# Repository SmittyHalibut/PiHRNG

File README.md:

# PiHRNG
#### It's pronounced "Pi Ring," or perhaps "Pie Ring" if you'd prefer.

A hardware random number generator on a Raspberry Pi hat.

More here later. (Famous last words, by @SmittyHalibut)

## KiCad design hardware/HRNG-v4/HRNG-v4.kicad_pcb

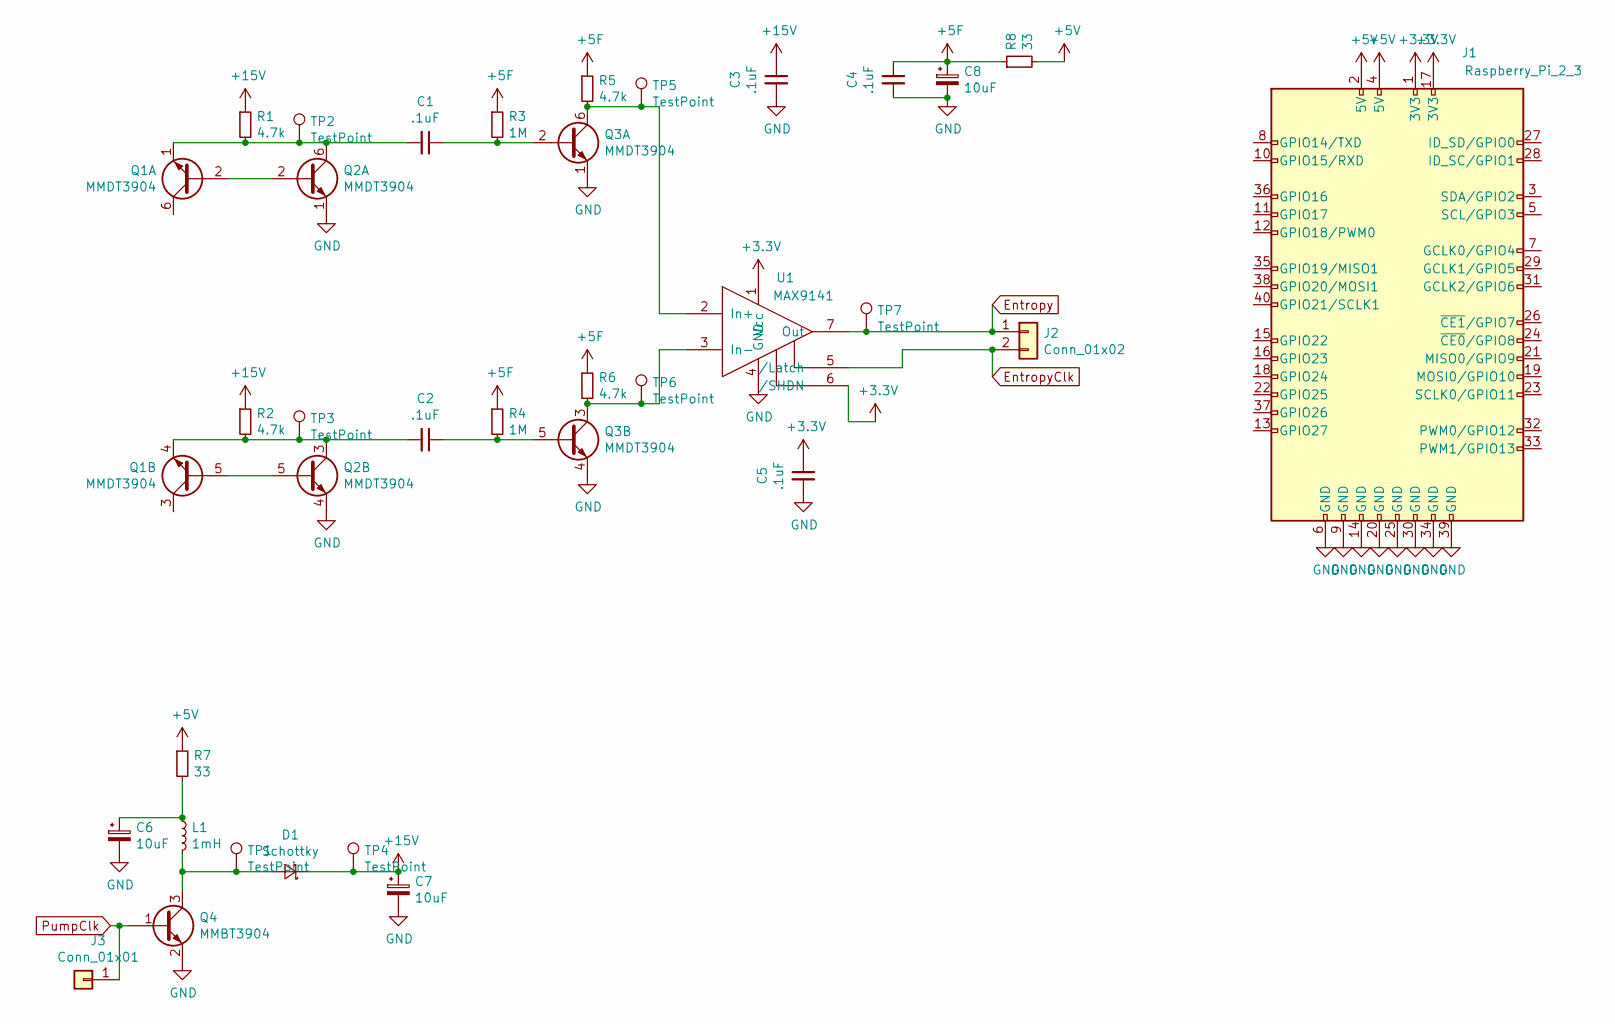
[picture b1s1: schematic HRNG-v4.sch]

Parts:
C1, C2, C3, C4, C5: .1uF; C_1206_3216Metric_Pad1.42x1.75mm_HandSolder
C6, C7, C8: 10uF; CP_Radial_D6.3mm_P2.50mm
D1: Schottky; D_1206_3216Metric_Pad1.42x1.75mm_HandSolder
J1: Raspberry_Pi_2_3; Raspberry_Pi_Zero_Socketed_THT_FaceDown_MountingHoles
J2: Conn_01x02; PinHeader_1x02_P2.54mm_Vertical
J3: Conn_01x01; PinHeader_1x01_P2.54mm_Vertical
L1: 1mH; L_1206_3216Metric_Pad1.42x1.75mm_HandSolder
Q1, Q2, Q3: MMDT3904; SOT-363_SC-70-6_Handsoldering
Q4: MMBT3904; SOT-23
R1, R2, R5, R6: 4.7k; R_1206_3216Metric_Pad1.42x1.75mm_HandSolder
R3, R4: 1M; R_1206_3216Metric_Pad1.42x1.75mm_HandSolder
R7, R8: 33; R_1206_3216Metric_Pad1.42x1.75mm_HandSolder
TP1, TP2, TP3, TP4, TP5, TP6, TP7: TestPoint; TestPoint_Pad_D1.5mm
U1: MAX9141; SOIC-8_3.9x4.9mm_P1.27mm

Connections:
+3V3: C5.1, J1.1 (3V3), J1.17 (3V3), U1.1 (Vcc), U1.6 (/SHDN)
+5F: C4.1, C8.1, R3.1, R4.1, R5.1, R6.1, R8.1
+5V: J1.2 (5V), J1.4 (5V), R7.1, R8.2
+15V: C3.1, C7.1, D1.1 (K), R1.1, R2.1, TP4.1
Entropy: J2.1, TP7.1, U1.7 (Out)
EntropyClk: J2.2, U1.5 (/Latch)
GND: C3.2, C4.2, C5.2, C6.2, C7.2, C8.2, J1.6 (GND), J1.9 (GND), J1.14 (GND), J1.20 (GND), J1.25 (GND), J1.30 (GND), J1.34 (GND), J1.39 (GND), Q2.1 (E1), Q2.4 (E2), Q3.1 (E1), Q3.4 (E2), Q4.2 (E), U1.4 (GND)
unnamed: C1.1, Q3.2 (B1), R3.2
unnamed: C1.2, Q1.1 (E1), Q2.6 (C1), R1.2, TP2.1
unnamed: C2.1, Q3.5 (B2), R4.2
unnamed: C2.2, Q1.4 (E2), Q2.3 (C2), R2.2, TP3.1
unnamed: C6.1, L1.1, R7.2
unnamed: D1.2 (A), L1.2, Q4.3 (C), TP1.1
unnamed: Q1.2 (B1), Q2.2 (B1)
unnamed: Q1.5 (B2), Q2.5 (B2)
unnamed: Q3.3 (C2), R6.2, TP6.1, U1.3 (In-)
unnamed: Q3.6 (C1), R5.2, TP5.1, U1.2 (In+)
PumpClk: J3.1, Q4.1 (B)

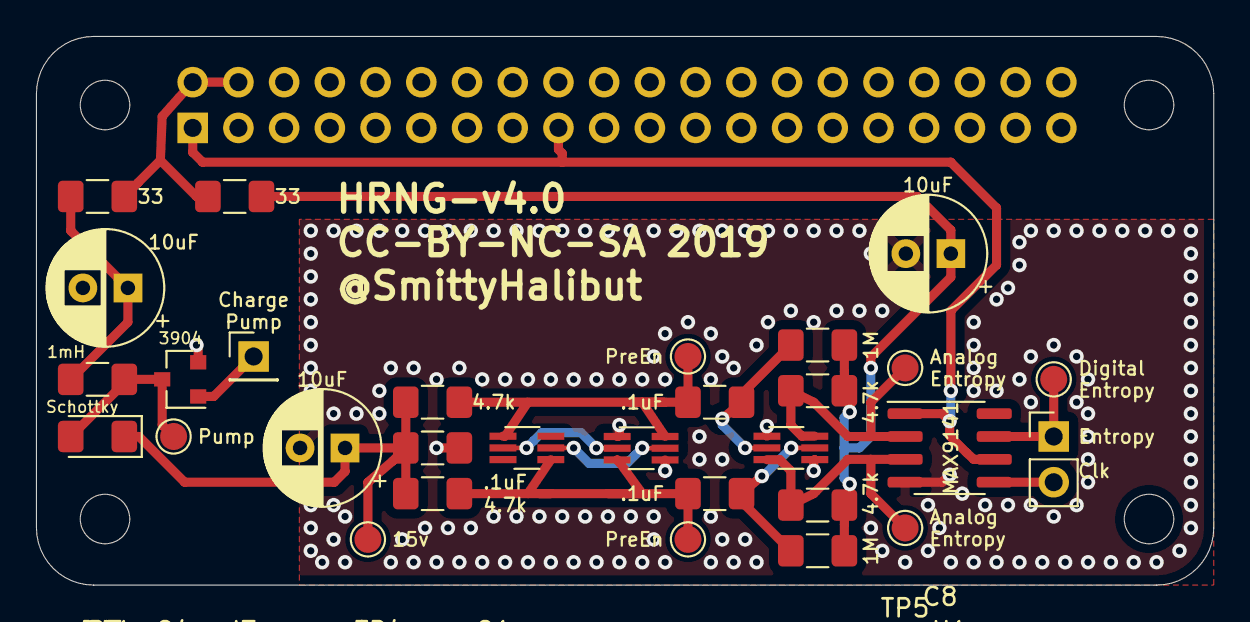
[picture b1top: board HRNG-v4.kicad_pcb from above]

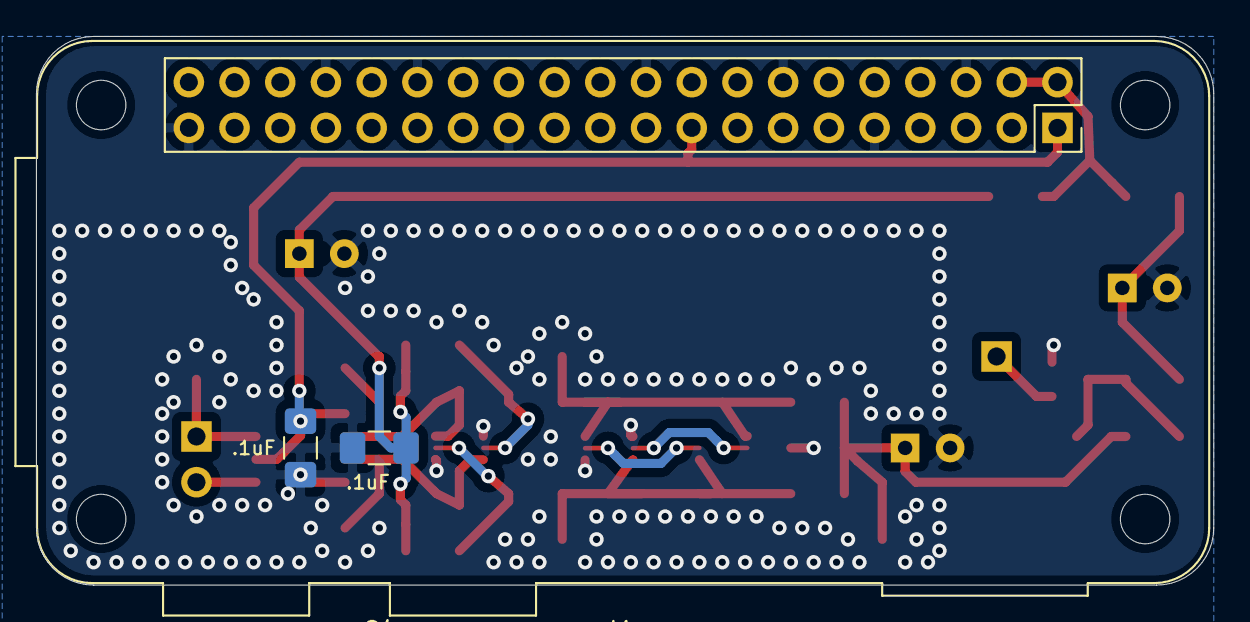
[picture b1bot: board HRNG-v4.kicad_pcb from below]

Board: 2 copper layers, 65.4 x 30.5 mm, 33 parts (3 on the bottom side), 18 nets.

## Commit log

2019-07-30 Initial commit of PiHRNG. Includes v1.0 of the board design, KiCAD 5.1 files.
2019-07-30 Added "Pie Ring" as a valid pronounciation of the project.
2019-07-30 Adding LICENSE

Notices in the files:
hardware/HRNG-v4/HRNG-v4.kicad_pcb:
CC-BY-NC-SA 2019
